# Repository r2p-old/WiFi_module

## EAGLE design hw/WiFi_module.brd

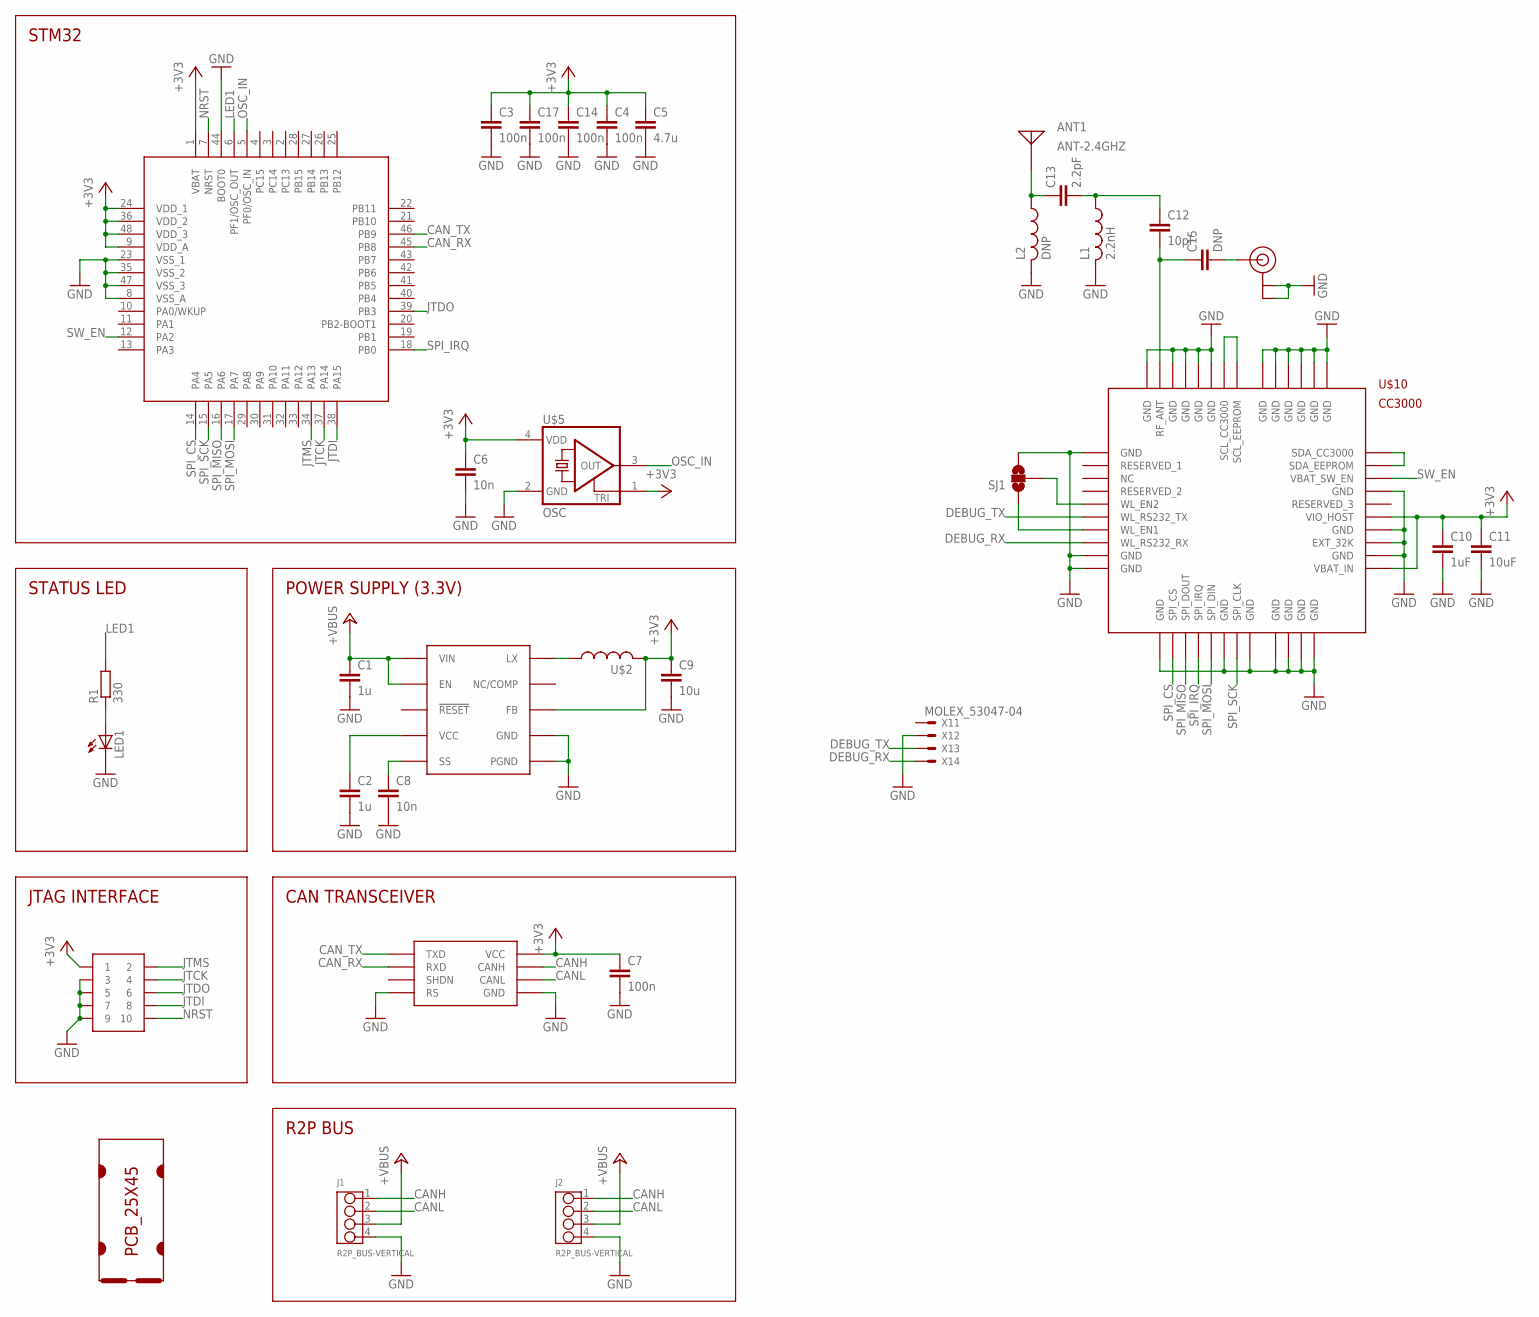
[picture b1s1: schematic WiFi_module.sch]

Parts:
ANT1: ANT-2.4GHZ; CHIP_ANTENNA_8X1
C1: 1u; C1206
C2: 1u; C0603
C3, C4, C7, C14, C17: 100n; C0603
C5: 4.7u; C0805
C6, C8: 10n; C0603
C9: 10u; C0805
C10: 1uF; C0603
C11: 10uF; C0805
C12: 10pF; C0402
C13: 2.2pF; C0402
C15: DNP; C0402
J1, J2: R2P_BUS-VERTICAL; OPL-EAGLE-LIBRARY_4P-2.0
L1: 2.2nH; L0402
L2: DNP; L0402
LED1: LED0805; CHIPLED_0805
R1: 330; R0603
SJ1: SOLDERJUMPER_2WAYPASTE1&2; SJ_3_PASTE1&2
SOT1: MAX3051EKA; SOT23-8L
U$1: PCB_25X45; 25X45
U$2: LPS4018; COILCRAFT_LPS4018
U$3: MAX17501; TDFN-10
U$4: JTAG-TH; SAMTEC_FTSH-105-TH
U$5: OSC; XTAL_2.5X2
U$6: STM32F303CTX; LQFP48
U$10: CC3000
U$11: U.FL
X1: MOLEX_53047-04

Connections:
+3V3: C3.1, C4.1, C5.1, C6.1, C7.1, C9.1, C10.1, C11.1, C14.1, C17.1, SOT1.3 (VCC), U$2.P$2 (2), U$3.P$5 (FB), U$4.1, U$5.1 (TRI), U$5.4 (VDD), U$6.1 (VBAT), U$6.9 (VDD_A), U$6.24 (VDD_1), U$6.36 (VDD_2), U$6.48 (VDD_3), U$10.P$19 (VBAT_IN), U$10.P$23 (VIO_HOST)
+VBUS: C1.1, J1.3, J2.3, U$3.P$2 (VIN), U$3.P$3 (EN)
CANH: J1.1, J2.1, SOT1.7 (CANH)
CANL: J1.2, J2.2, SOT1.6 (CANL)
CAN_RX: SOT1.4 (RXD), U$6.45 (PB8)
CAN_TX: SOT1.1 (TXD), U$6.46 (PB9)
DEBUG_RX: U$10.P$8 (WL_RS232_RX), X1.4
DEBUG_TX: U$10.P$6 (WL_RS232_TX), X1.3
GND: C1.2, C2.2, C3.2, C4.2, C5.2, C6.2, C7.2, C8.2, C9.2, C10.2, C11.2, C14.2, C17.2, J1.4, J2.4, L1.2, L2.2, LED1.C, SJ1.3, SOT1.2 (GND), SOT1.8 (RS), U$3.P$1 (PGND), U$3.P$9 (GND), U$3.P$11 (PGND), U$4.3, U$4.5, U$4.7, U$4.9, U$5.2 (GND), U$6.8 (VSS_A), U$6.23 (VSS_1), U$6.35 (VSS_2), U$6.44 (BOOT0), U$6.47 (VSS_3), U$10.P$1 (GND), U$10.P$9 (GND), U$10.P$10 (GND), U$10.P$11 (GND), U$10.P$16 (GND), U$10.P$18 (GND), U$10.P$20 (GND), U$10.P$21 (EXT_32K), U$10.P$22 (GND), U$10.P$25 (GND), U$10.P$31 (GND), U$10.P$32 (GND), U$10.P$33 (GND), U$10.P$34 (GND), U$10.P$36 (GND), U$10.P$37 (GND), U$10.P$38 (GND), U$10.P$39 (GND), U$10.P$40 (GND), U$10.P$41 (GND), U$10.P$42 (GND), U$10.P$43 (GND), U$10.P$44 (GND), U$10.P$45 (GND), U$10.P$46 (GND), U$11.P$1 (GND), U$11.P$2 (GND), X1.2
JTCK: U$4.4, U$6.37 (PA14)
JTDI: U$4.8, U$6.38 (PA15)
JTDO: U$4.6, U$6.39 (PB3)
JTMS: U$4.2, U$6.34 (PA13)
LED1: R1.2, U$6.6 (PF1/OSC_OUT)
unnamed: U$2.P$1 (1), U$3.P$10 (LX)
unnamed: SJ1.1, U$10.P$7 (WL_EN1)
unnamed: LED1.A, R1.1
unnamed: SJ1.2, U$10.P$5 (WL_EN2)
unnamed: C12.1, C13.2, L1.1
unnamed: C2.1, U$3.P$4 (VCC)
unnamed: C8.1, U$3.P$6 (SS)
unnamed: ANT1.P$1, C13.1, L2.1
unnamed: C15.2, U$11.P$3 (SIGNAL)
unnamed: U$10.P$27 (SDA_EEPROM), U$10.P$28 (SDA_CC3000)
unnamed: U$10.P$29 (SCL_EEPROM), U$10.P$30 (SCL_CC3000)
unnamed: C12.2, C15.1, U$10.P$35 (RF_ANT)
NRST: U$4.10, U$6.7 (NRST)
OSC_IN: U$5.3 (OUT), U$6.5 (PF0/OSC_IN)
SPI_CS: U$6.14 (PA4), U$10.P$12 (SPI_CS)
SPI_IRQ: U$6.18 (PB0), U$10.P$14 (SPI_IRQ)
SPI_MISO: U$6.16 (PA6), U$10.P$13 (SPI_DOUT)
SPI_MOSI: U$6.17 (PA7), U$10.P$15 (SPI_DIN)
SPI_SCK: U$6.15 (PA5), U$10.P$17 (SPI_CLK)
SW_EN: U$6.12 (PA2), U$10.P$26 (VBAT_SW_EN)

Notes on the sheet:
STM32
STATUS LED
JTAG INTERFACE
POWER SUPPLY (3.3V)
CAN TRANSCEIVER
R2P BUS

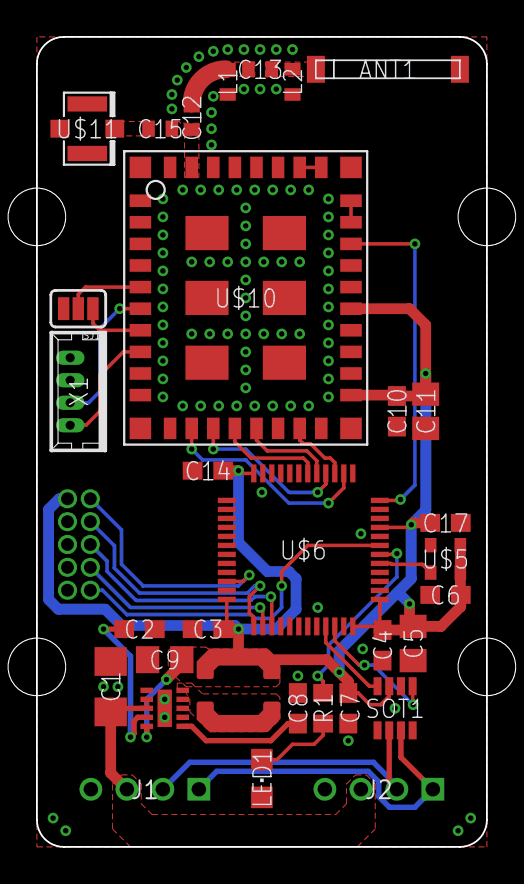
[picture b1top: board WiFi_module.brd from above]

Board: 2 copper layers, 25.0 x 45.0 mm, 34 parts (0 on the bottom side), 34 nets.

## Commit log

2015-02-07 Rename
2015-02-07 Working on layout
2015-02-09 Working on RF layout
2015-02-09 Layout complete
2015-02-19 Fixed directory creation
2015-02-19 Fixed silkscreen

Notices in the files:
parts and their libraries:
SparkFun: Licensing: CC v3.0 Share-Alike You are welcome to use this library for commercial purposes.
